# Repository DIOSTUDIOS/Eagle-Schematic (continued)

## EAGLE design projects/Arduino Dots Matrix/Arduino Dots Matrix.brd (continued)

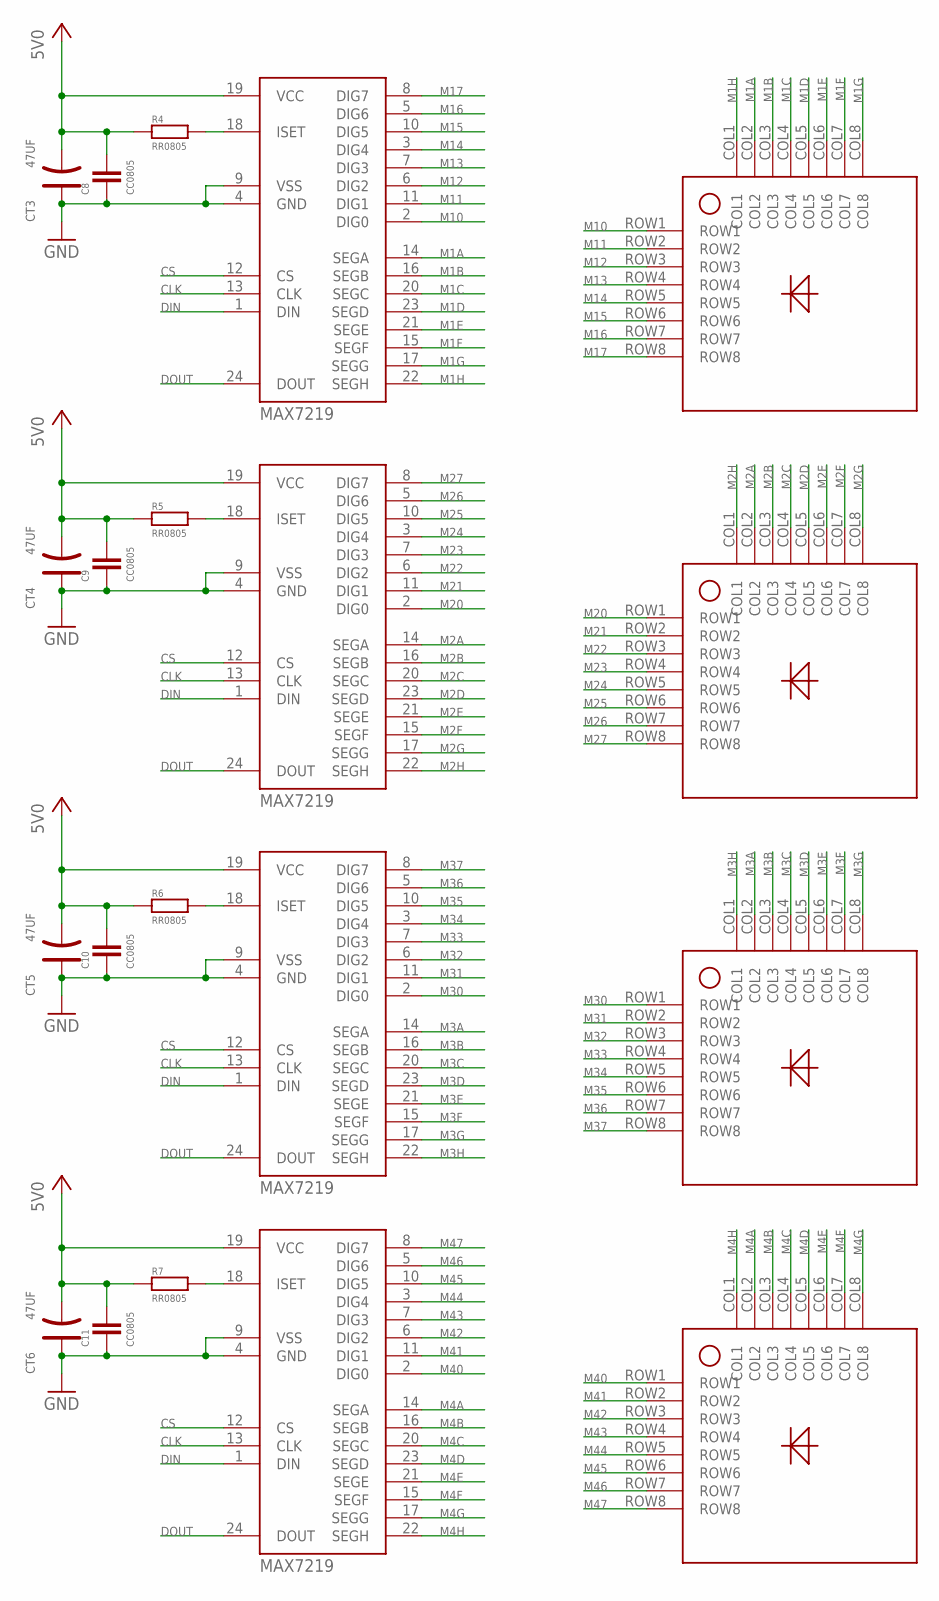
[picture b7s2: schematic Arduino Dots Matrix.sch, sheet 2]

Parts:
C8, C9, C10, C11: CC0805; C0805
CT3, CT4, CT5, CT6: 47UF; ELECTRO-SMD-C-6MM
D1, D2, D3, D4: DOT-MATRIX-AS; 1088AS
M1, M2, M3, M4: MAX7219; SOP24
R4, R5, R6, R7: RR0805; R0805

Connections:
+5V: C8.1, C9.1, C10.1, C11.1, CT3.-, CT4.-, CT5.-, CT6.-, M1.19 (VCC), M2.19 (VCC), M3.19 (VCC), M4.19 (VCC), R4.1, R5.1, R6.1, R7.1; also elsewhere on the board
CLK: M1.13 (CLK), M2.13 (CLK), M3.13 (CLK), M4.13 (CLK)
CS: M1.12 (CS), M2.12 (CS), M3.12 (CS), M4.12 (CS)
DIN: M1.1 (DIN), M2.1 (DIN), M3.1 (DIN), M4.1 (DIN)
DOUT: M1.24 (DOUT), M2.24 (DOUT), M3.24 (DOUT), M4.24 (DOUT)
GND: C8.2, C9.2, C10.2, C11.2, CT3.+, CT4.+, CT5.+, CT6.+, M1.4 (GND), M1.9 (VSS), M2.4 (GND), M2.9 (VSS), M3.4 (GND), M3.9 (VSS), M4.4 (GND), M4.9 (VSS); also elsewhere on the board
M1A: D1.COL2, M1.14 (SEGA)
M1B: D1.COL3, M1.16 (SEGB)
M1C: D1.COL4, M1.20 (SEGC)
M1D: D1.COL5, M1.23 (SEGD)
M1E: D1.COL6, M1.21 (SEGE)
M1F: D1.COL7, M1.15 (SEGF)
M1G: D1.COL8, M1.17 (SEGG)
M1H: D1.COL1, M1.22 (SEGH)
M2A: D2.COL2, M2.14 (SEGA)
M2B: D2.COL3, M2.16 (SEGB)
M2C: D2.COL4, M2.20 (SEGC)
M2D: D2.COL5, M2.23 (SEGD)
M2E: D2.COL6, M2.21 (SEGE)
M2F: D2.COL7, M2.15 (SEGF)
M2G: D2.COL8, M2.17 (SEGG)
M2H: D2.COL1, M2.22 (SEGH)
M3A: D3.COL2, M3.14 (SEGA)
M3B: D3.COL3, M3.16 (SEGB)
M3C: D3.COL4, M3.20 (SEGC)
M3D: D3.COL5, M3.23 (SEGD)
M3E: D3.COL6, M3.21 (SEGE)
M3F: D3.COL7, M3.15 (SEGF)
M3G: D3.COL8, M3.17 (SEGG)
M3H: D3.COL1, M3.22 (SEGH)
M4A: D4.COL2, M4.14 (SEGA)
M4B: D4.COL3, M4.16 (SEGB)
M4C: D4.COL4, M4.20 (SEGC)
M4D: D4.COL5, M4.23 (SEGD)
M4E: D4.COL6, M4.21 (SEGE)
M4F: D4.COL7, M4.15 (SEGF)
M4G: D4.COL8, M4.17 (SEGG)
M4H: D4.COL1, M4.22 (SEGH)
M10: D1.ROW1, M1.2 (DIG0)
M11: D1.ROW2, M1.11 (DIG1)
M12: D1.ROW3, M1.6 (DIG2)
M13: D1.ROW4, M1.7 (DIG3)
M14: D1.ROW5, M1.3 (DIG4)
M15: D1.ROW6, M1.10 (DIG5)
M16: D1.ROW7, M1.5 (DIG6)
M17: D1.ROW8, M1.8 (DIG7)
M20: D2.ROW1, M2.2 (DIG0)
M21: D2.ROW2, M2.11 (DIG1)
M22: D2.ROW3, M2.6 (DIG2)
M23: D2.ROW4, M2.7 (DIG3)
M24: D2.ROW5, M2.3 (DIG4)
M25: D2.ROW6, M2.10 (DIG5)
M26: D2.ROW7, M2.5 (DIG6)
M27: D2.ROW8, M2.8 (DIG7)
M30: D3.ROW1, M3.2 (DIG0)
M31: D3.ROW2, M3.11 (DIG1)
M32: D3.ROW3, M3.6 (DIG2)
M33: D3.ROW4, M3.7 (DIG3)
M34: D3.ROW5, M3.3 (DIG4)
M35: D3.ROW6, M3.10 (DIG5)
M36: D3.ROW7, M3.5 (DIG6)
M37: D3.ROW8, M3.8 (DIG7)
M40: D4.ROW1, M4.2 (DIG0)
M41: D4.ROW2, M4.11 (DIG1)
M42: D4.ROW3, M4.6 (DIG2)
M43: D4.ROW4, M4.7 (DIG3)
M44: D4.ROW5, M4.3 (DIG4)
M45: D4.ROW6, M4.10 (DIG5)
M46: D4.ROW7, M4.5 (DIG6)
M47: D4.ROW8, M4.8 (DIG7)
unnamed: M1.18 (ISET), R4.2
unnamed: M2.18 (ISET), R5.2
unnamed: M3.18 (ISET), R6.2
unnamed: M4.18 (ISET), R7.2

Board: 2 copper layers, 40 parts (0 on the bottom side), 83 nets, no tracks yet.

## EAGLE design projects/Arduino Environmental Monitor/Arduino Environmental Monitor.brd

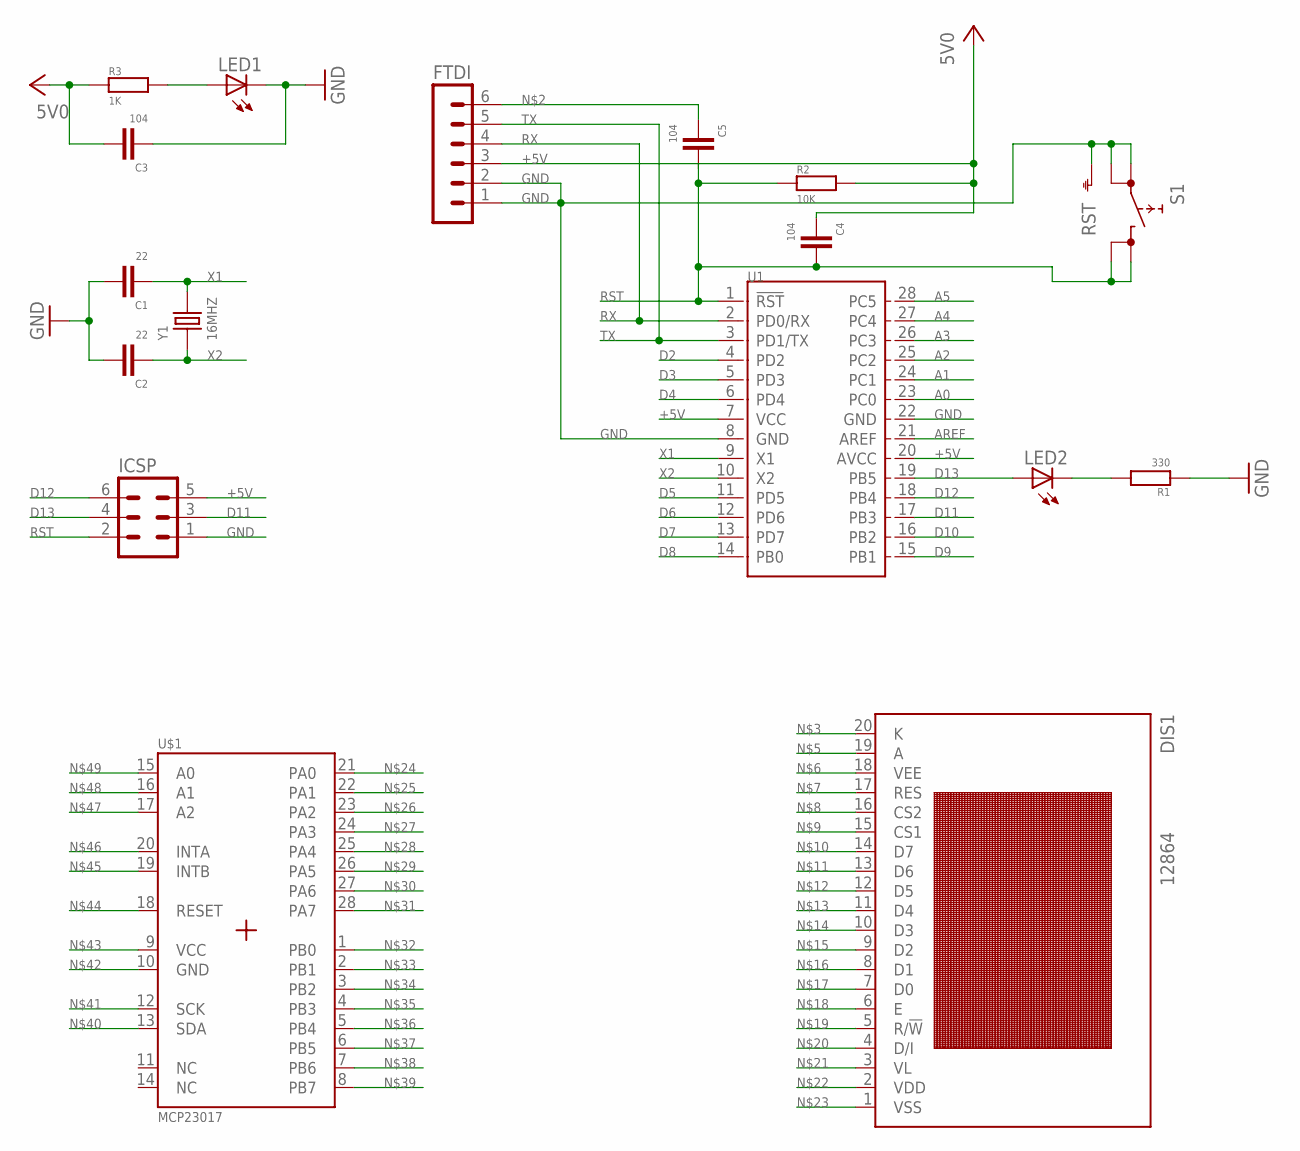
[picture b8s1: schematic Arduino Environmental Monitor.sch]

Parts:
C1, C2: 22; C0805
C3, C4, C5: 104; C0805
DIS1: 12864; LCD128X64
FTDI: MA06-1
ICSP: MA03-2
LED1, LED2: LEDCHIPLED_0805; CHIPLED_0805
R1: 330; R0805
R2: 10K; R0805
R3: 1K; R0805
S1: RST; SKHMPXE010
U1: MCU-ATMEGA328P-PU(DIP28); DIP28-2.54-35.6X13.5MM
U$1: MCP23017; SO28W
Y1: 16MHZ; HC49US

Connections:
+5V: C3.1, C4.2, FTDI.3, ICSP.5, R2.2, R3.1, U1.7 (VCC), U1.20 (AVCC)
A0: U1.23 (PC0)
A1: U1.24 (PC1)
A2: U1.25 (PC2)
A3: U1.26 (PC3)
A4: U1.27 (PC4)
A5: U1.28 (PC5)
AREF: U1.21 (AREF)
D2: U1.4 (PD2)
D3: U1.5 (PD3)
D4: U1.6 (PD4)
D5: U1.11 (PD5)
D6: U1.12 (PD6)
D7: U1.13 (PD7)
D8: U1.14 (PB0)
D9: U1.15 (PB1)
D10: U1.16 (PB2)
D11: ICSP.3, U1.17 (PB3)
D12: ICSP.6, U1.18 (PB4)
D13: ICSP.4, LED2.A, U1.19 (PB5)
GND: C1.1, C2.1, C3.2, FTDI.1, FTDI.2, ICSP.1, LED1.C, R1.1, S1.1 (1.1), S1.2 (1.2), S1.5 (SH), U1.8 (GND), U1.22 (GND)
unnamed: LED1.A, R3.2
unnamed: C5.2, FTDI.6
unnamed: LED2.C, R1.2
RST: C4.1, ICSP.2, R2.1, S1.3 (2.1), S1.4 (2.2), U1.1 (!RST)
RX: FTDI.4, U1.2 (PD0/RX)
TX: FTDI.5, U1.3 (PD1/TX)
X1: C1.2, U1.9 (X1), Y1.2
X2: C2.2, U1.10 (X2), Y1.1

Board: 2 copper layers, 17 parts (0 on the bottom side), 13 nets, no tracks yet.

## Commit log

2020-05-09 2020.05.09.01
2020-05-17 2020.05.18.01
2020-05-21 2020.05.21.01
2020-05-25 2020.05.25.01
2020-05-27 2020.05.27.01
2020-06-01 2020.06.01.01
2020-06-03 2020.06.03.01
2020-06-05 2020.06.05.01
2020-06-08 2020.06.08.01
2020-06-11 2020.06.11.01
2020-06-12 2020.06.12.01
2020-06-12 2020.06.12.02
2020-06-16 2020.06.16.01
2020-06-18 2020.06.18.01
2020-06-19 2020.06.19.01
2020-06-21 2020.06.21.01
2020-06-22 2020.06.22.01
2020-06-24 2020.06.24.01
2020-06-24 2020.06.24.02
2020-06-24 2020.06.24.03
2020-06-24 2020.06.24.04
2020-06-26 2020.06.26.01
2020-06-27 2020.06.27.01
2020-06-29 2020.06.30.01
2020-06-30 2020.06.30.02
2020-07-01 2020.07.01.01
2020-07-01 2020.07.01.02
2020-07-02 2020.07.02.01
2020-07-02 2020.07.03.01
2020-07-03 2020.07.03.02
2020-07-05 2020.07.05.01
2020-07-07 2020.07.07.01
2020-07-07 2020.07.08.01
2020-07-08 2020.07.09.01
2020-07-09 2020.07.09.02
2020-07-13 2020.07.13.01
2020-07-15 2020.07.15.01
2020-07-15 2020.07.15.02
